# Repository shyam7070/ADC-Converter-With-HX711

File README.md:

# ADC-Converter-With-HX711

This project is an ADC (Analog-to-Digital Converter) system designed using the HX711 load cell amplifier module, developed in KiCad. HX711 is a precision 24-bit analog-to-digital converter widely used in weight measurement and load cell applications.

# Project Overview
Project Name: ADC Converter with HX711
Platform: KiCad
Module Used: HX711 Load Cell Amplifier
Functionality: Converts analog signals from sensors (such as load cells) into digital signals with high accuracy and stability.

# Features
24-bit precision ADC conversion.
Designed in KiCad with a clean PCB layout and schematic.
Interface with microcontrollers (such as Arduino, ESP32, or PIC).
Compact PCB design for easy integration into various measurement systems.
Support for differential inputs for better noise rejection.

# Hardware Components
HX711 Module: 24-bit ADC for precise load cell measurements.
Microcontroller Interface Pins: For connecting with Arduino/ESP32.
Load Cell Connections: For connecting to the load cell’s output terminals.
Power Supply: 3.3V or 5V (depending on microcontroller compatibility).

# KiCad Design Files
Schematic: Complete schematic designed in KiCad with component references.
PCB Layout: Optimized PCB design for minimal noise and stable ADC readings.
BOM (Bill of Materials): List of all components used in the project.
Gerber Files: Ready for PCB fabrication.

# How to Use
1. Connect the load cell to the HX711 module input pins.
2. Interface the HX711 output with a microcontroller.
3. Power the system with the required voltage.
4. Use Arduino/PIC/ESP32 libraries to read the ADC values from HX711.
5. Calibrate the system for accurate load measurement.

# Applications
Digital weighing scales
Industrial load measurement
Force sensing applications
Precision instrumentation

# Author
Narasingarao K
+917075025629
knrkondapalli123@gmail.com

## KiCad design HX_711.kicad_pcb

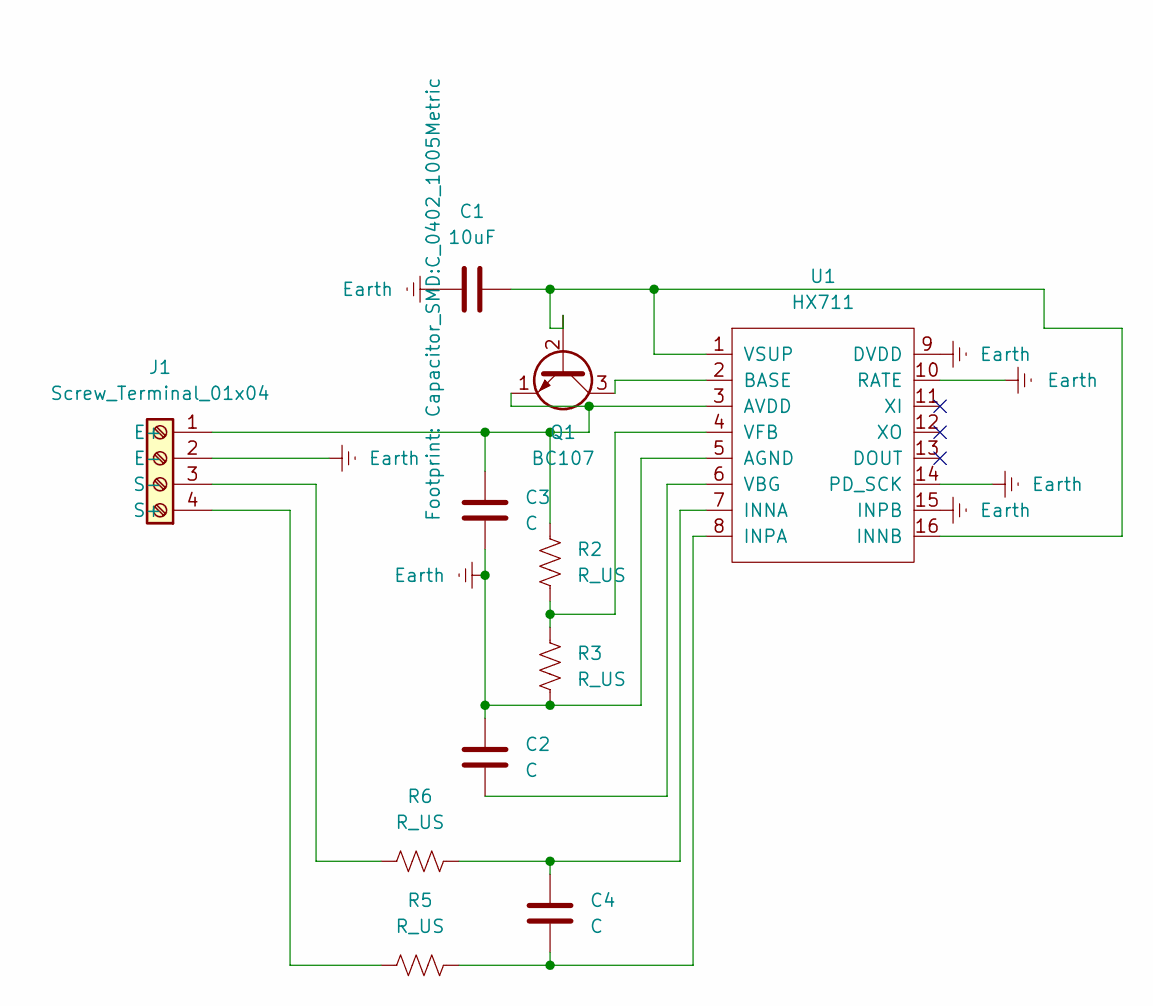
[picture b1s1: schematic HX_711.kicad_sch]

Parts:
C1: 10uF; C_0402_1005Metric
C2, C3, C4: C; C_0201_0603Metric
J1: Screw_Terminal_01x04; TerminalBlock_Xinya_XY308-2.54-4P_1x04_P2.54mm_Horizontal
Q1: BC107; TO-18-3
R2, R3, R5, R6: R_US; R_0201_0603Metric
U1: HX711; HX7111

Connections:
Earth: C1.2, C2.1, C3.2, J1.2 (E-), R3.2, U1.5 (AGND), U1.9 (DVDD), U1.10 (RATE), U1.14 (PD_SCK), U1.15 (INPB)
unnamed: C3.1, J1.1 (E+), Q1.1 (E), R2.1, U1.3 (AVDD)
unnamed: J1.4 (S+), R5.1
unnamed: J1.3 (S-), R6.1
unnamed: C1.1, Q1.2 (B), U1.1 (VSUP), U1.16 (INNB)
unnamed: Q1.3 (C), U1.2 (BASE)
unnamed: C4.1, R6.2, U1.7 (INNA)
unnamed: C4.2, R5.2, U1.8 (INPA)
unnamed: C2.2, U1.6 (VBG)
unnamed: R2.2, R3.1, U1.4 (VFB)

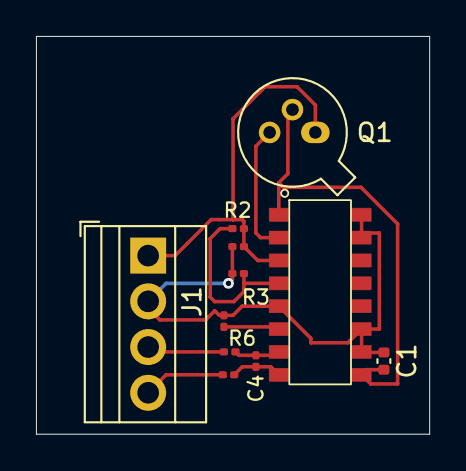
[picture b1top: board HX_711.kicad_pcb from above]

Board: 2 copper layers, 21.8 x 22.1 mm, 11 parts (0 on the bottom side), 10 nets.

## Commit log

2025-02-16 README.md
